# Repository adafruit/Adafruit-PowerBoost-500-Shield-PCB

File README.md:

## Adafruit PowerBoost 500 Shield PCB
<a href="http://www.adafruit.com/products/2078"><br/>
Click here to purchase one from the Adafruit shop</a>

The PowerBoost shield! This stackable shield goes onto your Arduino and provides a slim rechargeable power pack, with a built in battery charger as well as DC/DC booster.

Compatible with Adafruit Metro, Arduino Uno, Duemilanove, Mega, Leonardo and Due - basically any Arduino-pinout-shaped Arduino as only the GND and 5V pins are used. You can stack shields on top, or stack the PowerBoost on top. Please note that the powerboost does not pass through the ICSP headers (the battery is in the way) so if your stacking shield uses ICSP for data transfer (like the Ethernet Shield), you'll need to stack the PowerBoost above it!

The PowerBoost shield can run off of any Lithium Ion or Lithium Polymer battery (3.7/4.2V kind) but we suggest our 1200mAh capacity  or 2000mAh capacity batteries, both of which fits very nicely in the empty space of the shield. Plug in the battery and recharge it via the microUSB jack. When you're ready to go, just unplug the Arduino from USB or the wall adapter and it will automatically switch over to shield power. Use only Lipoly batteries with protection circuitry!

The onboard boost converter can provide at least 500mA current, and can peak at 1A. There's an onboard fuse to protect against higher current draws which could damage the boost converter or battery. The boost converter can be damaged by high current spikes and is not recommended for driving motors or robots where the stall current can cause high current spikes

PCB files for the Adafruit PowerBoost 500 Shield. The format is EagleCAD schematic and board layout
- https://www.adafruit.com/product/2078

### License

Adafruit invests time and resources providing this open source design, please support Adafruit and open-source hardware by purchasing products from [Adafruit](https://www.adafruit.com)!

All text above must be included in any redistribution

Designed by Limor Fried/Ladyada for Adafruit Industries.
Creative Commons Attribution/Share-Alike, all text above must be included in any redistribution. 
See license.txt for additional information.

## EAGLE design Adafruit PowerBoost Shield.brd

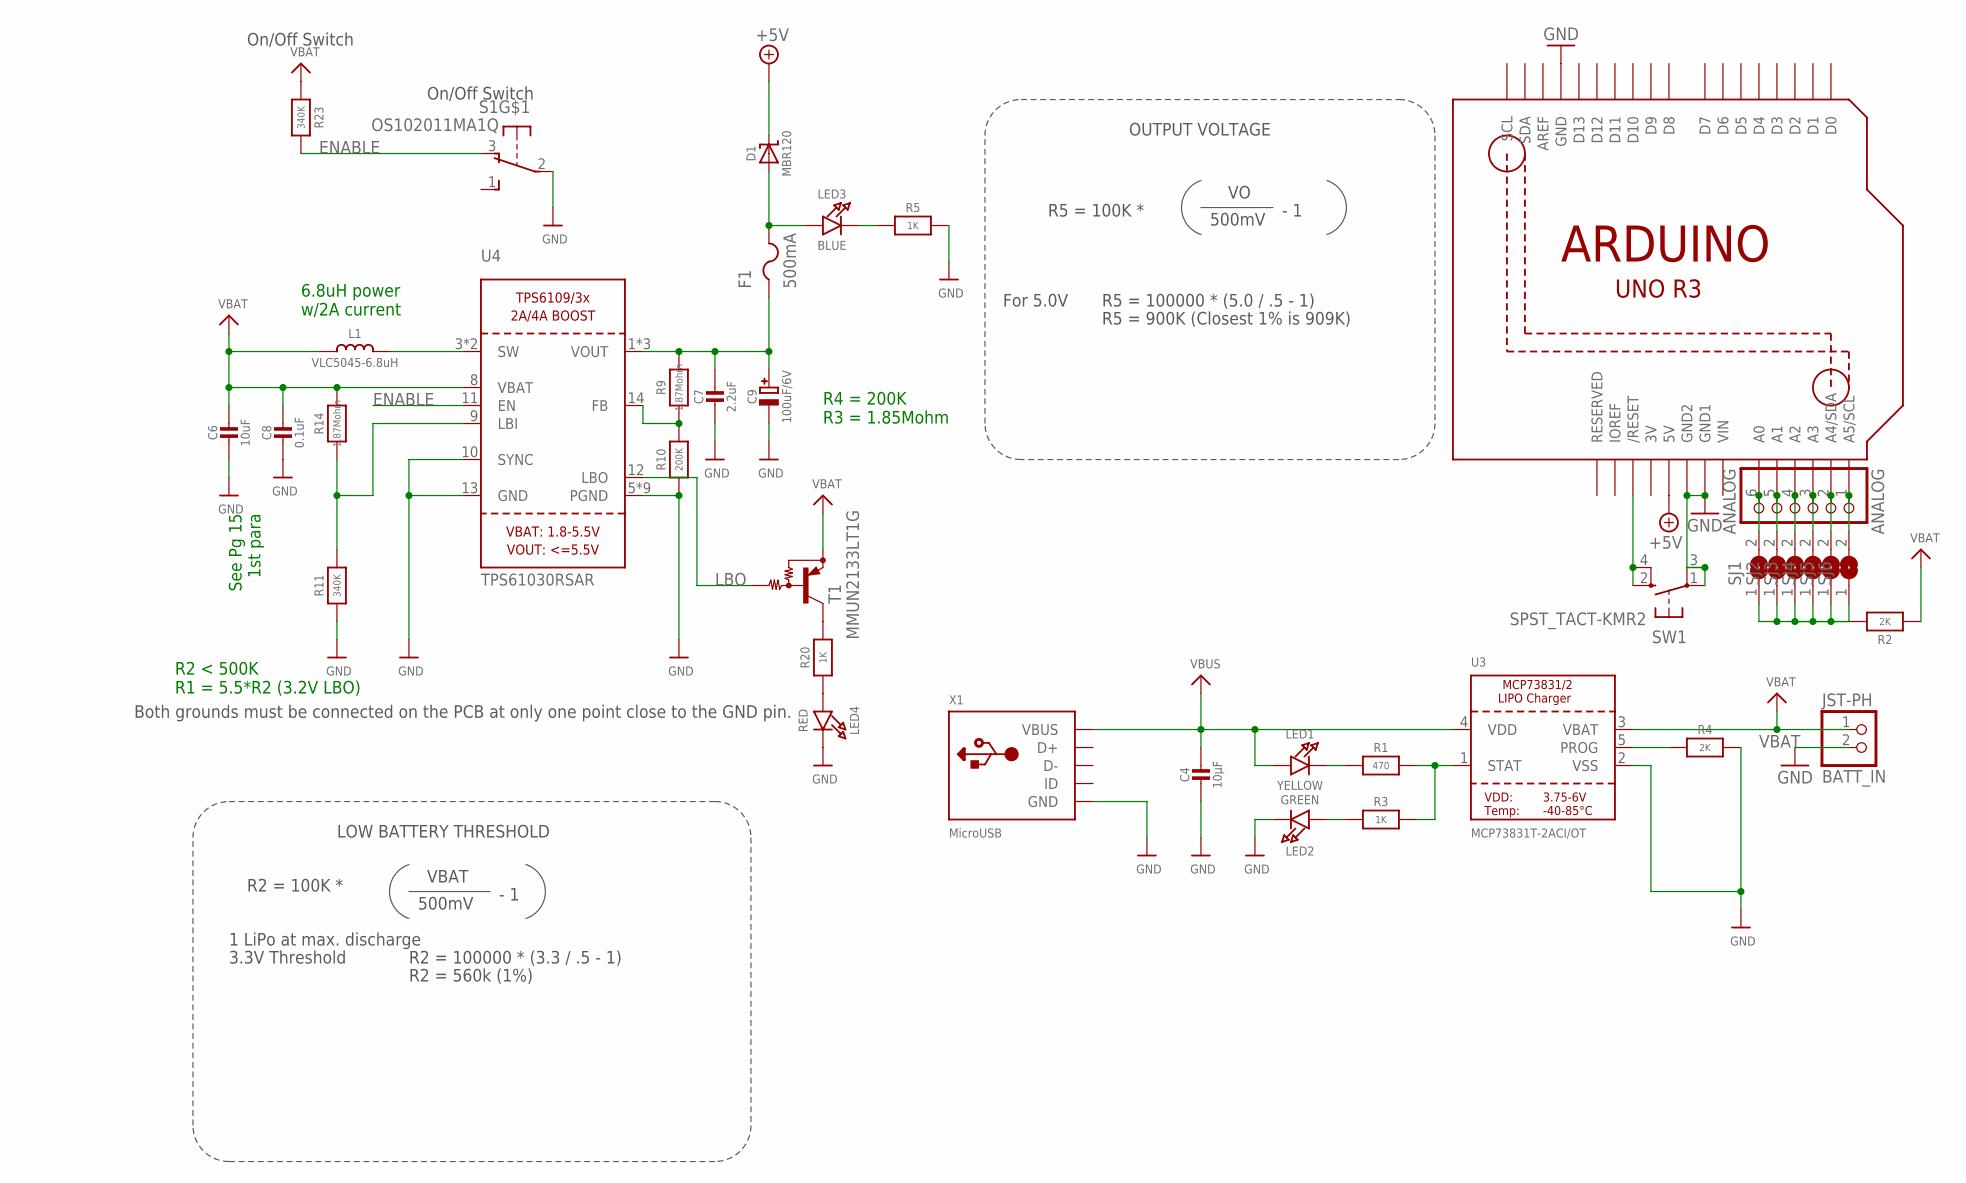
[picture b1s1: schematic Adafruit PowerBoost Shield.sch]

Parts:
ANALOG: ANALOG; 1X06
BATT_IN: JST-PH; JST-PH-2-SMT
C4: 10µF; 0805-NO
C6: 10uF; 0805-NO
C7: 2.2uF; 0805-NO
C8: 0.1uF; 0805-NO
C9: 100uF/6V; EIA3528-21/B-R
D1: MBR120; SOD-123
F1: 500mA; R1206
L1: VLC5045-6.8uH; INDUCTOR_5X5MM_TDK_VLC5045
LED1: YELLOW; CHIPLED_0805_NOOUTLINE
LED2: GREEN; CHIPLED_0805_NOOUTLINE
LED3: BLUE; CHIPLED_0805_NOOUTLINE
LED4: RED; CHIPLED_0805_NOOUTLINE
R1: 470; 0805-NO
R2, R4: 2K; 0805-NO
R3, R5, R20: 1K; 0805-NO
R9, R14: 1.87Mohm; 0805-NO
R10: 200K; 0805-NO
R11, R23: 340K; 0805-NO
S1: OS102011MA1Q
SJ1, SJ2, SJ3, SJ4, SJ5, SJ6: SOLDERJUMPER; SOLDERJUMPER_ARROW_NOPASTE
SW1: SPST_TACT-KMR2; KMR2
T1: MMUN2133LT1G; SC59-BEC
U2: ARDUINOR3-NOSILK
U3: MCP73831T-2ACI/OT; SOT23-5
U4: TPS61030RSAR; PVQFN-16
U$3, U$4: FIDUCIAL; FIDUCIAL_1MM
X1: MicroUSB; 4UCONN_20329

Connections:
3V: U2.3V
+5V: D1.C, U2.5V
A0: ANALOG.6, SJ1.2, U2.A0
A1: ANALOG.5, SJ2.2, U2.A1
A2: ANALOG.4, SJ3.2, U2.A2
A3: ANALOG.3, SJ4.2, U2.A3
A4: ANALOG.2, SJ5.2, U2.A4 (A4/SDA)
A5: ANALOG.1, SJ6.2, U2.A5 (A5/SCL)
ENABLE: R23.2, S1.3 (O), U4.11 (EN)
FB: R9.1, R10.2, U4.14 (FB)
GND: BATT_IN.2 (1), C4.2, C6.2, C7.2, C8.2, C9.-, LED2.C, LED4.C, R4.2, R5.2, R10.1, R11.1, S1.2, SW1.1, SW1.3 (P1), U2.GND, U2.GND1, U2.GND2, U3.2 (VSS), U4.5 (PGND), U4.6 (PGND), U4.7 (PGND), U4.10 (SYNC), U4.13 (GND), U4.P$18 (PGND), U4.P$19 (PGND), U4.P$20 (PGND), U4.P$21 (PGND), U4.P$22 (PGND), U4.THERMAL (PGND), X1.BASE@1 (GND), X1.BASE@2 (GND), X1.GND, X1.SPRT@1 (GND), X1.SPRT@2 (GND), X1.SPRT@3 (GND), X1.SPRT@4 (GND)
LBI: R11.2, R14.1, U4.9 (LBI)
LBO: T1.B, U4.12 (LBO)
unnamed: R2.2, SJ1.1, SJ2.1, SJ3.1, SJ4.1, SJ5.1, SJ6.1
unnamed: LED1.C, R1.1
unnamed: R1.2, R3.2, U3.1 (STAT)
unnamed: L1.P$2 (2), U4.3 (SW), U4.4 (SW)
unnamed: R4.1, U3.5 (PROG)
unnamed: LED2.A, R3.1
unnamed: LED3.C, R5.1
unnamed: LED4.A, R20.1
unnamed: R20.2, T1.C
unnamed: D1.A, F1.2, LED3.A
RESET: SW1.2 (S), SW1.4 (S1), U2.RESET (/RESET)
VBAT: BATT_IN.1 (2), C6.1, C8.1, L1.P$1 (1), R2.1, R14.2, R23.1, T1.E, U3.3 (VBAT), U4.8 (VBAT)
VBUS: C4.1, LED1.A, U3.4 (VDD), X1.VBUS
VIN: U2.VIN
VOUT: C7.1, C9.+, F1.1, R9.2, U4.1 (VOUT), U4.15 (VOUT), U4.16 (VOUT)

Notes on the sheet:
R2 = 100K *
VBAT
500mV
- 1
3.3V Threshold
R2 = 100000 * (3.3 / .5 - 1)
LOW BATTERY THRESHOLD
OUTPUT VOLTAGE
R5 = 100K *
For 5.0V
R5 = 100000 * (5.0 / .5 - 1)
R5 = 900K (Closest 1% is 909K)
1 LiPo at max. discharge
On/Off Switch
R2 = 560k (1%)
Both grounds must be connected on the PCB at only one point close to the GND pin.
See Pg 15 1st para
6.8uH power w/2A current
R2 < 500K R1 = 5.5*R2 (3.2V LBO)
R4 = 200K R3 = 1.85Mohm

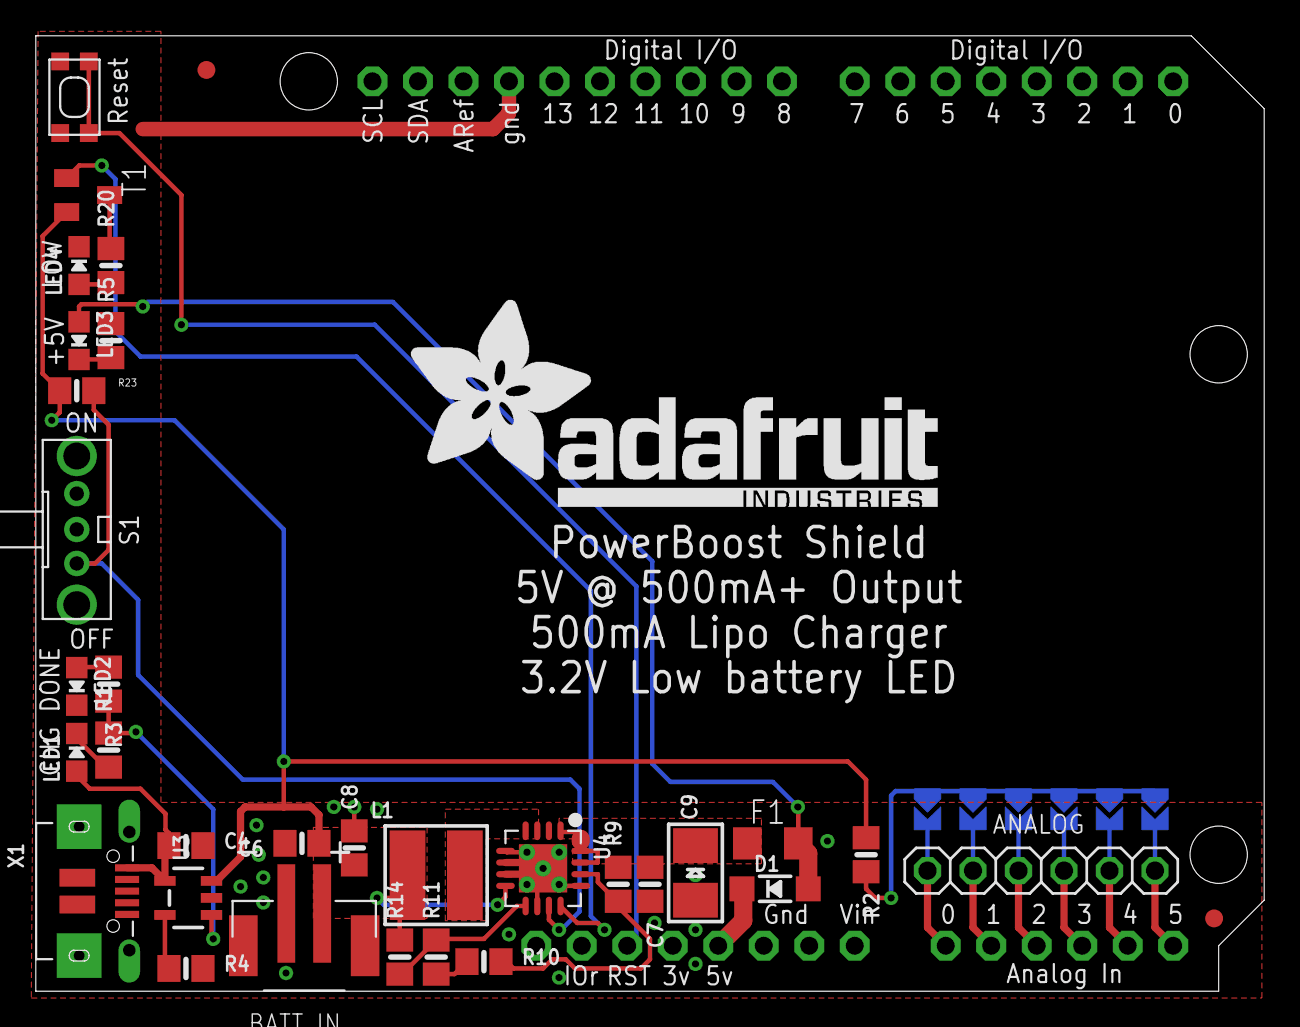
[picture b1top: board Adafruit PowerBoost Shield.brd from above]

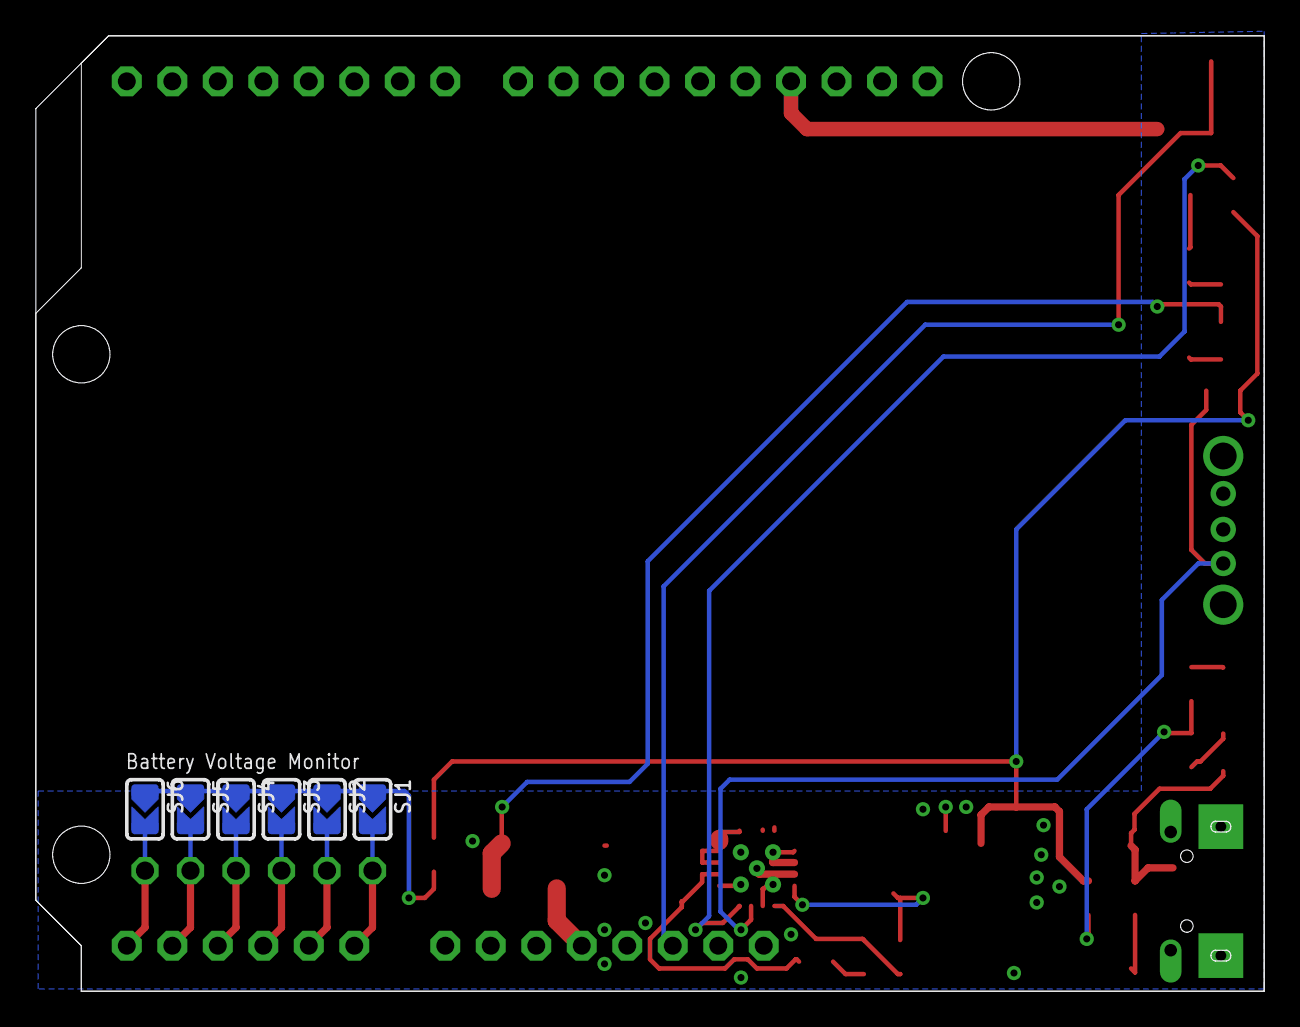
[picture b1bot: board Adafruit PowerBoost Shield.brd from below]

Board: 2 copper layers, 68.6 x 53.3 mm, 41 parts (6 on the bottom side), 26 nets.

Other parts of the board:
U$6: ADAFRUIT_TEXT_30MM

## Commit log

2016-08-03 init
